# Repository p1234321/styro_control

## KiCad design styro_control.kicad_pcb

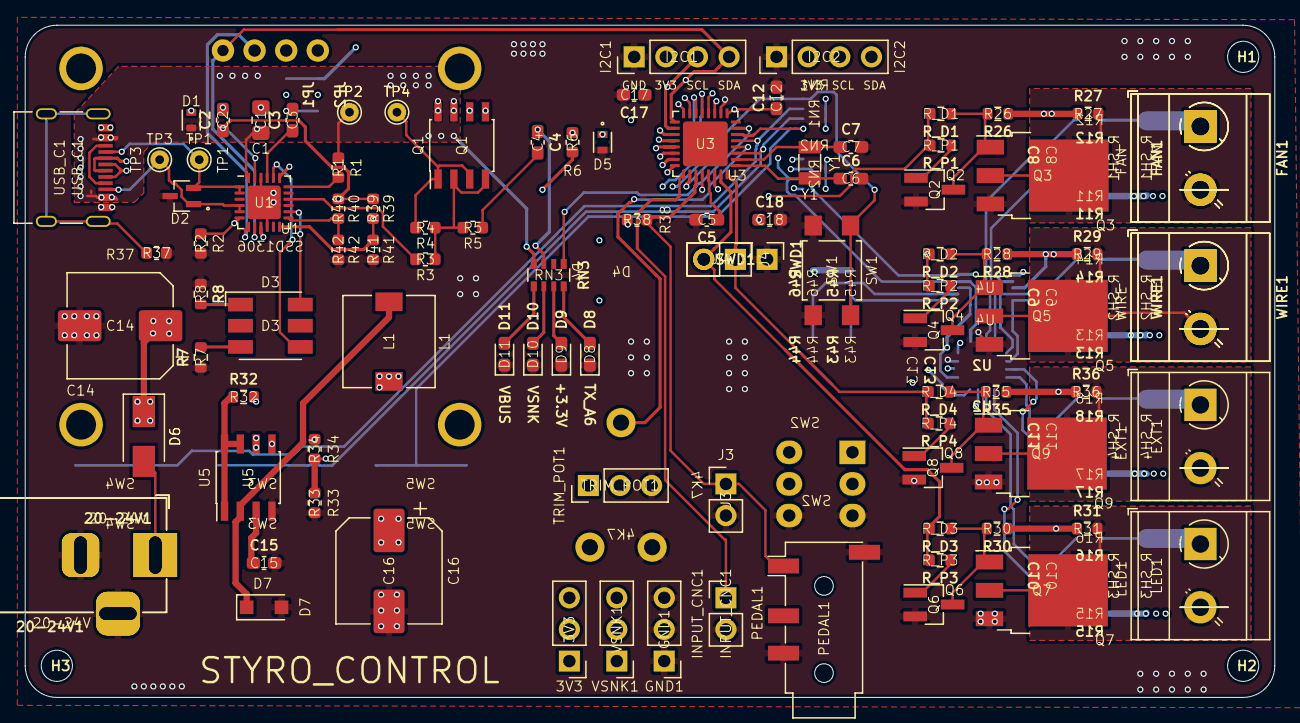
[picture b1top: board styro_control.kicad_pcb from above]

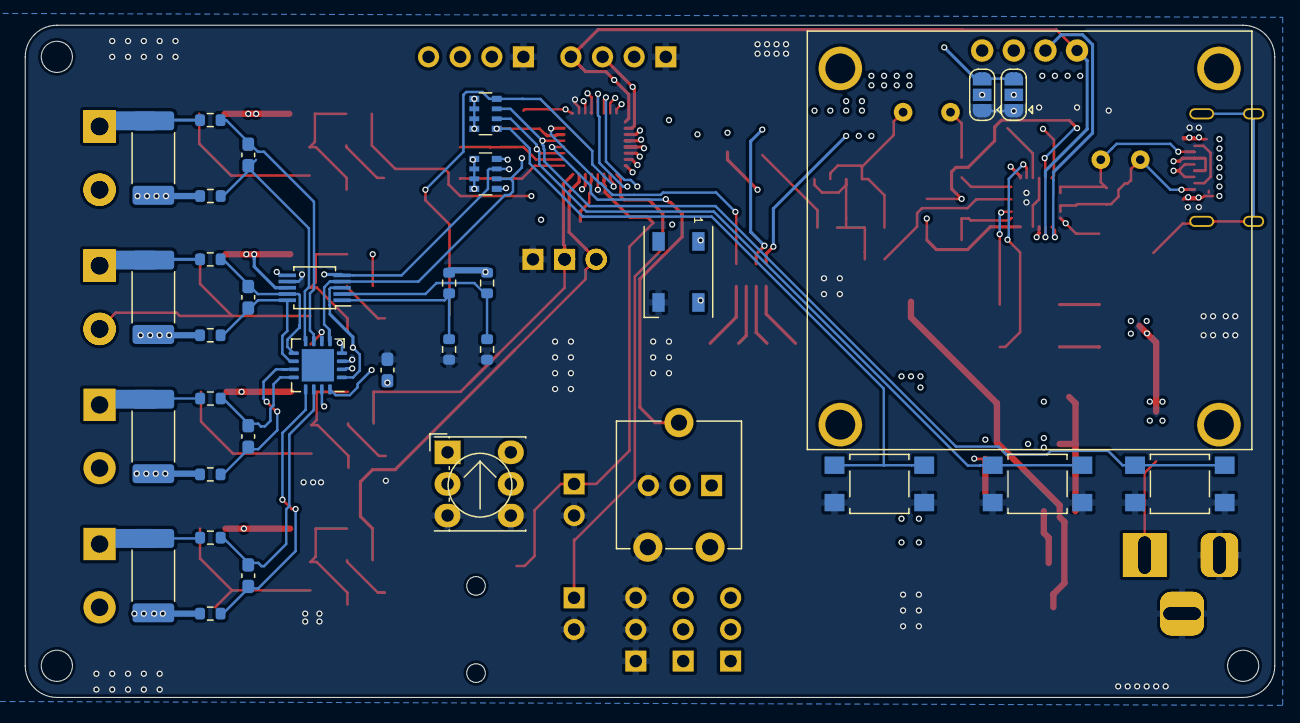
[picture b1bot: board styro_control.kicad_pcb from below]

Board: 4 copper layers, 100.3 x 54.0 mm, 133 parts (34 on the bottom side), 85 nets.

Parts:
3V3: +3V3; PinHeader_1x03_P2.54mm_Vertical
4K7: R_POT_TRIM; Potentiometer_ACP_CA9-V10_Vertical
20-24V, 20-24V1: Barrel_Jack_Switch; BarrelJack_Horizontal
C1: 4,7uF; C_0805_2012Metric_Pad1.15x1.40mm_HandSolder
C2, C3, C4, C12, C17, C18: 100nF; C_0603_1608Metric_Pad1.08x0.95mm_HandSolder
C5: 1uF; C_0603_1608Metric_Pad1.08x0.95mm_HandSolder
C6, C7, C8, C9, C10, C11, C13: C; C_0603_1608Metric_Pad1.08x0.95mm_HandSolder
C14: 100uF; CP_Elec_8x10
C15: 180pF; C_0603_1608Metric_Pad1.08x0.95mm_HandSolder
C16: 22uF; CP_Elec_8x10
D1, D5: ESDA25P35-1U1M; TVS_ESDA25P35-1U1M
D2: ESDA25W; SOT65P210X110-3N
D3: LED_RGB; LED_RGB_5050-6
D4: WS2812B; LED_WS2812B_PLCC4_5.0x5.0mm_P3.2mm
D6: D_Schottky; D_SMA
D7: 1N5189; D_SOD-123F
D8: VBUS; LED_0603_1608Metric_Pad1.05x0.95mm_HandSolder
D9: VSNK; LED_0603_1608Metric_Pad1.05x0.95mm_HandSolder
D10: +3.3V; LED_0603_1608Metric_Pad1.05x0.95mm_HandSolder
D11: TX_A6; LED_0603_1608Metric_Pad1.05x0.95mm_HandSolder
EXT1: EXT_CONTROL; TerminalBlock_MetzConnect_Type073_RT02602HBLU_1x02_P5.08mm_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
FAN, FAN1: FAN_CONTROL; TerminalBlock_MetzConnect_Type073_RT02602HBLU_1x02_P5.08mm_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
GND1: GND; PinHeader_1x03_P2.54mm_Vertical
H1, H2, H3: MountingHole; MountingHole_2.5mm
I2C1: -; PinHeader_1x04_P2.54mm_Vertical
I2C2: I2C2; PinHeader_1x04_P2.54mm_Vertical
INPUT_CNC1: INPUT_CNC; PinHeader_1x02_P2.54mm_Vertical
J3: INPUT_PEDAL; PinHeader_1x02_P2.54mm_Vertical
J4: SWD; PinHeader_1x02_P2.54mm_Vertical
JP1, JP2: SolderJumper_3_Open; SolderJumper-3_P1.3mm_Open_RoundedPad1.0x1.5mm
L1: 470uH; L_7.3x7.3_H3.5
LED1: LED_CONTROL; TerminalBlock_MetzConnect_Type073_RT02602HBLU_1x02_P5.08mm_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
PEDAL1: AudioJack4; Jack_3.5mm_PJ320D_Horizontal
Q1: IRF7324; SOIC-8_3.9x4.9mm_P1.27mm
Q2, Q4, Q6, Q8: Q_NPN_BEC; SOT-23_Handsoldering
Q3, Q5, Q7, Q9: Q_NMOS_GDS; TO-252-3_TabPin2
R1, R6, R7, R8: 1k; R_0603_1608Metric
R2, R33: 10K; R_0603_1608Metric
R3, R41, R42, R43, R44: 22k; R_0603_1608Metric
R4: 100k; R_0603_1608Metric
R5, R37: 100; R_0603_1608Metric
R11, R12, R13, R14, R15, R16, R17, R18, R26, R27, R28, R29, R30, R31, R35, R36, R38: R; R_0603_1608Metric
R32: 0R18; R_0603_1608Metric
R34: 16K; R_0603_1608Metric
R39, R40, R45, R46: DNP; R_0603_1608Metric
RN1, RN3: R_Pack04; R_Array_Convex_4x0603
RN2: 4k7; R_Array_Convex_4x0603
R_D1, R_D2, R_D3, R_D4: R; R_0603_1608Metric
R_P1, R_P2, R_P3, R_P4: R; R_0603_1608Metric
R_SH1, R_SH2, R_SH3, R_SH4: 0,02R; R_2512_6332Metric_Pad1.52x3.35mm_HandSolder
SSD1306: SSD1306; SSD1306_I2c
SW1: SW_RESET; SW_4.5x4.5
SW2: switch_6_pin; standard_switch
SW3: SW_1; SW_4.5x4.5
SW4: SW_2; SW_4.5x4.5
SW5: SW_3; SW_4.5x4.5
SWD1: SWD; PinHeader_1x03_P2.54mm_Vertical
TP1: CC1; TestPoint_THTPad_D1.5mm_Drill0.7mm
TP2: VBUS; TestPoint_THTPad_D1.5mm_Drill0.7mm
TP3: CC2; TestPoint_THTPad_D1.5mm_Drill0.7mm
TP4: SOURCE; TestPoint_THTPad_D1.5mm_Drill0.7mm
TRIM_POT1: TRIM_POT; PinHeader_1x03_P2.54mm_Vertical
U1: STUSB4500QTR; QFN-24-1EP_4x4mm_P0.5mm_EP2.7x2.7mm
U2: PAC1932-4; UQFN-16-1EP_4x4mm_P0.65mm_EP2.6x2.6mm
U3: ATSAMD21E18A-M; QFN-32-1EP_5x5mm_P0.5mm_EP3.6x3.6mm
U4: INA226; MSOP-10_3x3mm_P0.5mm
U5: MC34063AD_copy; SOIC-8_3.9x4.9mm_P1.27mm
USB_C1: USB_C_Receptacle_USB2.0; USB_C_Receptacle_Palconn_UTC16-G
VSNK1: VSNK; PinHeader_1x03_P2.54mm_Vertical
WIRE, WIRE1: HEAT_CONTROL; TerminalBlock_MetzConnect_Type073_RT02602HBLU_1x02_P5.08mm_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
Y1: Crystal; Crystal_SMD_3215-2Pin_3.2x1.5mm

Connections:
+3V3: 3V3.1, 3V3.2, 3V3.3, 4K7.1, C12.1, C13.1, C16.1, C17.1, C18.1, I2C1.2, I2C2.2, JP1.3 (B), JP2.3 (B), L1.2, R34.2, R38.1, R45.1, R46.1, RN1.1 (R1.1), RN1.2 (R2.1), RN1.3 (R3.1), RN1.4 (R4.1), RN2.1 (R1.1), RN2.2 (R2.1), RN2.3 (R3.1), RN2.4 (R4.1), TRIM_POT1.1, U2.2 (VDD), U2.15 (VDDIO), U3.9 (VDDANA), U3.30 (VDDIN), U4.6 (Vs)
/2V7: C2.1, R39.1, R40.1, U1.23 (VREG_2V7)
/A0: RN1.6 (R3.2), SW3.2, U3.3 (PA02)
/A2: RN1.7 (R2.2), SW4.2, U3.5 (PA04)
/A3: RN1.5 (R4.2), SW5.2, U3.6 (PA05)
/ALERT: RN2.5 (R4.2), U1.19 (ALERT), U3.11 (PA08)
/D+: U3.24 (PA25), USB_C1.A6 (D+), USB_C1.B6 (D+)
/D-: U3.23 (PA24), USB_C1.A7 (D-), USB_C1.B7 (D-)
/EC: J4.1, R_D4.2, R_P4.2, SWD1.2, U3.32 (PA31)
/EXT_SINK: EXT1.1, R18.2, R_SH4.1
/FAN_CONTROL/DRAIN: FAN.2, FAN1.2, Q3.2 (D), R27.2
/FAN_SINK: FAN.1, FAN1.1, R12.2, R_SH1.1
/FC: R_D1.2, R_P1.2, U3.19 (PA18)
/HC: R_D2.2, R_P2.2, U3.20 (PA19)
/HEAT_CONTROL/DRAIN: Q5.2 (D), R29.2, WIRE.2, WIRE1.2
/HEAT_SINK: R14.2, R_SH2.1, WIRE.1, WIRE1.1
/IN1: INPUT_CNC1.1, U3.25 (PA27)
/IN2: J3.1, PEDAL1.T, R38.2, SW2.2 (C), U3.27 (PA28)
/LC: J4.2, RN2.8 (R1.2), R_D3.2, R_P3.2, SWD1.3, U3.31 (PA30)
/LED_CONTROL/DRAIN: LED1.2, Q7.2 (D), R31.2
/LED_SINK: LED1.1, R16.2, R_SH3.1
/POT: 4K7.2, TRIM_POT1.2, U3.4 (PA03)
/PWRDN: U2.16 (~PWRDN), U3.15 (PA14)
/RES: RN1.8 (R1.2), SW1.1, U3.26 (~RESET)
/RESET: R2.1, U1.6 (RESET), U3.12 (PA09)
/SCL: I2C1.3, RN2.7 (R2.2), SSD1306.3 (SCL), U1.7 (SCL), U2.4 (SM_CLK), U3.18 (PA17), U4.5 (SCL)
/SCL2: I2C2.3, U3.22 (PA23)
/SDA: I2C1.4, RN2.6 (R3.2), SSD1306.4 (SDA), U1.8 (SDA), U2.5 (SM_DATA), U3.17 (PA16), U4.4 (SDA)
/SDA2: I2C2.4, U3.21 (PA22)
/SHIELD: R37.2, USB_C1.S1 (SHIELD)
/SLOW: U2.1 (SLOW/~ALERT), U3.16 (PA15), U4.3 (~Alert)
/TX_A6: RN3.1 (R1.1), U3.7 (PA06)
/VBUS: C1.2, D1.C, Q1.7 (D1), Q1.8 (D1), R1.1, RN3.4 (R4.1), TP2.1, U1.24 (VDD), USB_C1.A4 (VBUS), USB_C1.A9 (VBUS), USB_C1.B4 (VBUS), USB_C1.B9 (VBUS)
/VIN+: C9.2, R13.1, U2.10 (SENSE4+), U4.10 (Vin+)
/VIN-: C9.1, R14.1, U2.9 (SENSE4-), U4.9 (Vin-)
/VSNK: C4.1, C14.1, D5.C, D6.1 (K), Q1.5 (D2), Q1.6 (D2), R6.1, R11.2, R13.2, R15.2, R17.2, R26.1, R27.1, R28.1, R29.1, R30.1, R31.1, R32.2, R35.1, R36.1, RN3.3 (R3.1), R_SH1.2, R_SH2.2, R_SH3.2, R_SH4.2, U4.8 (Vbus), U5.6 (Vin), VSNK1.1, VSNK1.2, VSNK1.3
/WS_DIN: D4.4 (DIN), U3.13 (PA10)
/WS_EN: D4.1 (VDD), U3.14 (PA11)
/sheet60BBFA9B/DRAIN: EXT1.2, Q9.2 (D), R36.2
GND: 4K7.3, 20-24V.2, 20-24V.3, 20-24V1.2, 20-24V1.3, C1.1, C2.2, C3.2, C5.2, C6.2, C7.2, C12.2, C13.2, C14.2, C15.2, C16.2, C17.2, C18.2, D1.A, D2.3, D4.3 (VSS), D5.A, D7.2 (A), D8.1 (K), D9.1 (K), D10.1 (K), D11.1 (K), GND1.1, GND1.2, GND1.3, I2C1.1, I2C2.1, INPUT_CNC1.2, J3.2, JP1.1 (A), JP2.1 (A), PEDAL1.R2, PEDAL1.S, Q2.2 (E), Q3.3 (S), Q4.2 (E), Q5.3 (S), Q6.2 (E), Q7.3 (S), Q8.2 (E), Q9.3 (S), R2.2, R7.1, R8.1, R33.2, R37.1, R41.2, R42.2, R43.2, R44.2, SW1.2, SW2.3 (IN2), SW3.1, SW4.1, SW5.1, SWD1.1, TRIM_POT1.3, U1.10 (GND), U1.22 (VSYS), U1.25 (GND), U2.3 (GND), U2.6 (ADDRSEL), U3.10 (GND), U3.28 (GND), U4.7 (GND), U5.4 (GND), USB_C1.A1 (GND), USB_C1.A12 (GND), USB_C1.B1 (GND), USB_C1.B12 (GND)
unnamed: 20-24V.1, 20-24V1.1, D6.2 (A)
unnamed: C3.1, U1.21 (VREG_1V2)
unnamed: C4.2, R5.1
unnamed: C5.1, U3.29 (VDDCORE)
unnamed: C6.1, U3.1 (PA00), Y1.1
unnamed: C7.1, U3.2 (PA01), Y1.2
unnamed: C8.1, R12.1, U2.7 (SENSE3-)
unnamed: C8.2, R11.1, U2.8 (SENSE3+)
unnamed: C10.1, R16.1, U2.14 (SENSE2-)
unnamed: C10.2, R15.1, U2.13 (SENSE2+)
unnamed: C11.1, R18.1, U2.12 (SENSE1-)
unnamed: C11.2, R17.1, U2.11 (SENSE1+)
unnamed: C15.1, U5.3 (TC)
unnamed: D2.1, TP3.1, U1.4 (CC2), U1.5 (CC2DB), USB_C1.B5 (CC2)
unnamed: D2.2, TP1.1, U1.1 (CC1DB), U1.2 (CC1), USB_C1.A5 (CC1)
unnamed: D3.1 (RK), R8.2
unnamed: D3.3 (BK), R7.2
unnamed: D3.4 (BA), U1.20 (POWER_OK2)
unnamed: D3.6 (RA), U1.14 (POWER_OK3)
unnamed: D7.1 (K), L1.1, U5.2 (SwE)
unnamed: D8.2 (A), RN3.8 (R1.2)
unnamed: D9.2 (A), RN3.7 (R2.2)
unnamed: D10.2 (A), RN3.6 (R3.2)
unnamed: D11.2 (A), RN3.5 (R4.2)
unnamed: JP1.2 (C), SSD1306.2 (VCC)
unnamed: JP2.2 (C), SSD1306.1 (GND)
unnamed: Q1.1 (S1), Q1.3 (S2), R4.1, TP4.1
unnamed: Q1.2 (G1), Q1.4 (G2), R3.1, R4.2, R5.2
unnamed: Q2.1 (B), R_P1.1
unnamed: Q2.3 (C), Q3.1 (G), R26.2, R_D1.1
unnamed: Q4.1 (B), R_P2.1
unnamed: Q4.3 (C), Q5.1 (G), R28.2, R_D2.1
unnamed: Q6.1 (B), R_P3.1
unnamed: Q6.3 (C), Q7.1 (G), R30.2, R_D3.1
unnamed: Q8.1 (B), R_P4.1
unnamed: Q8.3 (C), Q9.1 (G), R35.2, R_D4.1
unnamed: R1.2, U1.18 (VBUS_VS_DISCH)
unnamed: R3.2, U1.16 (VBUS_EN_SNK)
unnamed: R6.2, U1.9 (DISCH)
unnamed: R32.1, U5.1 (SwC), U5.7 (Ipk), U5.8 (DC)
unnamed: R33.1, R34.1, U5.5 (Vfb)
unnamed: R39.2, R41.1, U1.12 (ADDR0)
unnamed: R40.2, R42.1, U1.13 (ADDR1)
unnamed: R43.1, R45.2, U4.1 (A1)
unnamed: R44.1, R46.2, U4.2 (A0)

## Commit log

2023-04-07 started adapting
2023-04-07 updated schematic
2023-04-07 added footprints
2023-04-11 added LEDs for VBUS,VSNK,3V3,TX
